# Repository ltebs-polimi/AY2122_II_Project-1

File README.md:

# AY2122_II_Project-1

## Pulseoximeter
The project involves the development of a portable pulseoximeter made using CY8CKIT-059 Development Kit by Cypress/Infineon and the MAX30101, a High-Sensitivity Pulse Oximeter and Heart-Rate Sensor for Wearable Health. Exploiting the circular buffer present inside the sensor, it is possible to extract the values coming from Infrared and Red LEDs and feed them inside a peak detection algorithm for PPG analysis, which outputs the SpO2 and Heart Rate values. Such function has been forked by the [MAX30101_Sensor_Library](https://github.com/sparkfun/SparkFun_MAX3010x_Sensor_Library/blob/master/src/spo2_algorithm.cpp) of the manufacturer Maxim Integrated; the function has been modified to our specific case. 
The project also involved the PCB design and production through press-n-print technique, the 3D case design and printing and the overall assembly of the final case.
## GUI

On the GUI it is also possible to make instant changes to the registers, which directly influence the MAX30101, such as the ADC range, the LED pulse width of the two LEDs, the LEDs pulse amplitude and the Sample Rate. These values will change the Full Scale Range of the readings, as well as the SNR (signal-to-noise-ratio).
## Final assembled device
The final device resembles a commercial pulseoximeter with a rudimental hinge that secures the finger in place over the photodiode, so that a constant pressure is applied. Moreover an internal coating was applied in order not to let light pass, so to assure a reliable sensor measure.

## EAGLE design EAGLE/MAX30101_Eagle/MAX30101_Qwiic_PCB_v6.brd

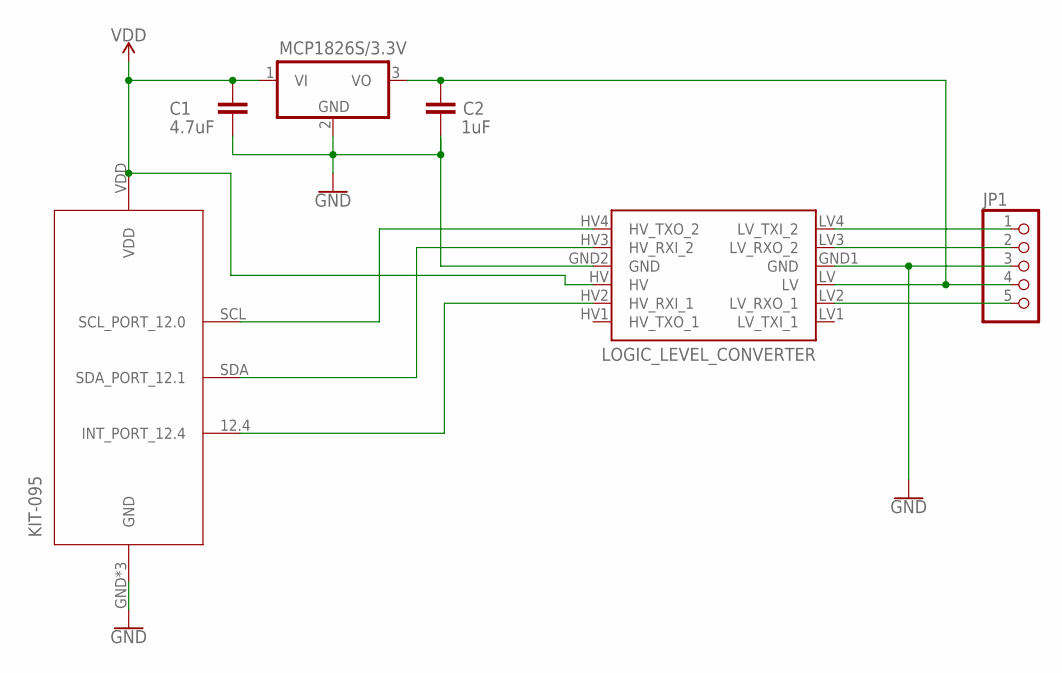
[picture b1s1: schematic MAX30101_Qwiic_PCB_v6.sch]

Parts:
C1: 4.7uF; CAP-PTH-SMALL-KIT
C2: 1uF; CAP-PTH-SMALL-KIT
IC1: 7805T; TO220H
JP1: PINHD-1X5/90; 1X05/90
KIT-095: KIT-095
LOGIC_LEVEL_CONVERTER: SPARKFUN_LOGIC_LEVEL_CONVERTER

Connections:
GND: C1.2, C2.2, IC1.2 (GND), JP1.3, KIT-095.GND, KIT-095.GND_ (GND), KIT-095._GND (GND), LOGIC_LEVEL_CONVERTER.GND1 (GND), LOGIC_LEVEL_CONVERTER.GND2 (GND)
unnamed: C2.1, IC1.3 (VO), JP1.4, LOGIC_LEVEL_CONVERTER.LV
unnamed: KIT-095.SCL (SCL_PORT_12.0), LOGIC_LEVEL_CONVERTER.HV4 (HV_TXO_2)
unnamed: KIT-095.SDA (SDA_PORT_12.1), LOGIC_LEVEL_CONVERTER.HV3 (HV_RXI_2)
unnamed: KIT-095.12.4 (INT_PORT_12.4), LOGIC_LEVEL_CONVERTER.HV2 (HV_RXI_1)
unnamed: JP1.1, LOGIC_LEVEL_CONVERTER.LV4 (LV_TXI_2)
unnamed: JP1.2, LOGIC_LEVEL_CONVERTER.LV3 (LV_RXO_2)
unnamed: JP1.5, LOGIC_LEVEL_CONVERTER.LV2 (LV_RXO_1)
VDD: C1.1, IC1.1 (VI), KIT-095.VDD, LOGIC_LEVEL_CONVERTER.HV

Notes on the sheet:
MCP1826S/3.3V

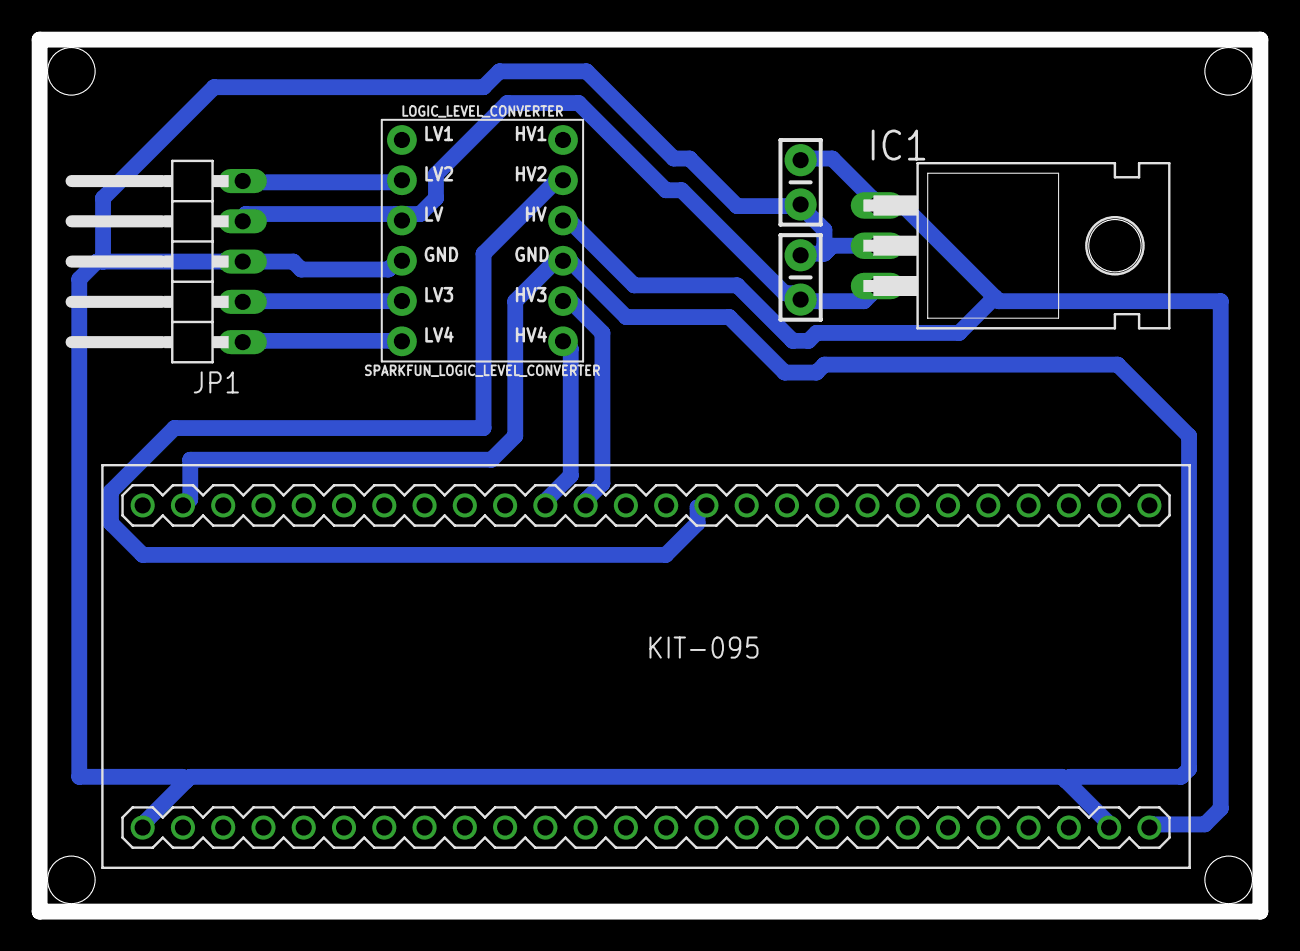
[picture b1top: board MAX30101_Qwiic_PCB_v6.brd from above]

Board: 2 copper layers, 77.0 x 55.0 mm, 6 parts (0 on the bottom side), 9 nets.

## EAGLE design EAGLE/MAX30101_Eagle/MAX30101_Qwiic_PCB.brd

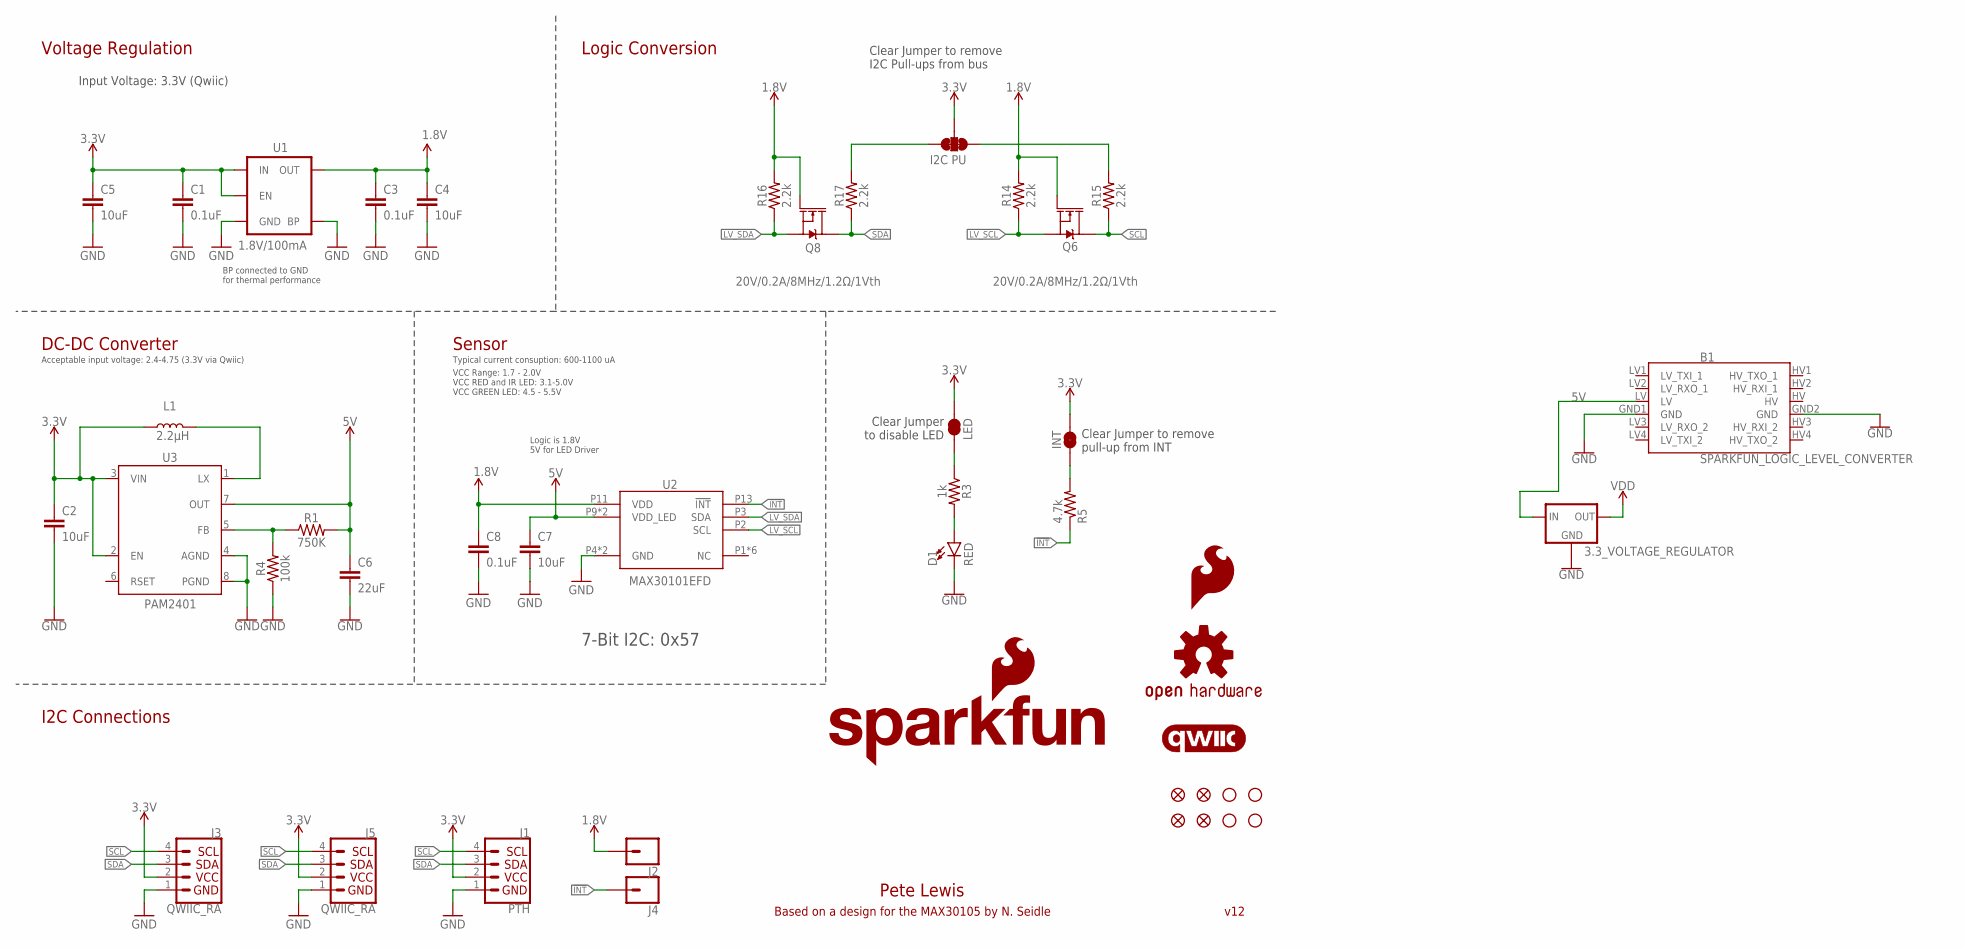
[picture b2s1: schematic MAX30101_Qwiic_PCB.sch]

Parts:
3.3_VOLTAGE_REGULATOR: V_REG_78XX-TO-220; TO-220-ALT
B1: SPARKFUN_LOGIC_LEVEL_CONVERTER
C1, C3, C8: 0.1uF; 0402
C2, C4, C5, C7: 10uF; 0603
C6: 22uF; 0805
D1: RED; LED-0603
FID1, FID2, FID3, FID4: FIDUCIAL1X2; FIDUCIAL-1X2
J1: PTH; 1X04_NO_SILK
J2, J4: CONN_01PTH_NO_SILK_YES_STOP; 1X01_NO_SILK
J3, J5: QWIIC_RA; JST04_1MM_RA
JP1: LED; SMT-JUMPER_2_NC_TRACE_SILK
JP2: INT; SMT-JUMPER_2_NC_TRACE_SILK
JP4: I2C PU; SMT-JUMPER_3_2-NC_TRACE_SILK
L1: 2.2μH; 0806
LOGO1: SFE_LOGO_NAME_FLAME.1_INCH; SFE_LOGO_NAME_FLAME_.1
LOGO2: OSHW-LOGOS; OSHW-LOGO-S
LOGO3: QWIIC_LOGO_5MM; QWIIC_5MM
LOGO4: SFE_LOGO_FLAME.1_INCH; SFE_LOGO_FLAME_.1
Q6, Q8: 20V/0.2A/8MHz/1.2Ω/1Vth; SOT-416FL
R1: 750K; 0603
R3: 1k; 0603
R4: 100k; 0603
R5: 4.7k; 0603
R14, R15, R16, R17: 2.2k; 0603
STANDOFF1, STANDOFF2, STANDOFF3, STANDOFF4: STAND-OFF
U1: 1.8V/100mA; SC70
U2: MAX30101EFD; 14_PIN_OESIP
U3: PAM2401; MSOP8

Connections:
1.8V: C3.1, C4.1, C8.1, J2.1, Q6.1 (G), Q8.1 (G), R14.2, R16.2, U1.5 (OUT), U2.P11 (VDD)
3.3V: C1.1, C2.1, C5.1, J1.2, J3.2, J5.2, JP1.2, JP2.2, JP4.2, L1.1, U1.1 (IN), U1.3 (EN), U3.2 (EN), U3.3 (VIN)
5V: C6.1, C7.1, R1.2, U2.P9 (VDD_LED), U2.P10 (VDD_LED), U3.7 (OUT)
!INT: J4.1, R5.1, U2.P13 (!INT)
GND: 3.3_VOLTAGE_REGULATOR.GND, B1.GND1 (GND), B1.GND2 (GND), C1.2, C2.2, C3.2, C4.2, C5.2, C6.2, C7.2, C8.2, D1.C, J1.1, J3.1, J5.1, R4.1, U1.2 (GND), U1.4 (BP), U2.P4 (GND), U2.P12 (GND), U3.4 (AGND), U3.8 (PGND)
HV: B1.HV
LV_SCL: Q6.2 (S), R14.1, U2.P2 (SCL)
LV_SDA: Q8.2 (S), R16.1, U2.P3 (SDA)
unnamed: JP2.1, R5.2
unnamed: R1.1, R4.2, U3.5 (FB)
unnamed: L1.2, U3.1 (LX)
unnamed: D1.A, R3.2
unnamed: JP4.3, R15.2
unnamed: JP4.1, R17.2
unnamed: 3.3_VOLTAGE_REGULATOR.IN, B1.LV
unnamed: JP1.1, R3.1
SCL: J1.4, J3.4, J5.4, Q6.3 (D), R15.1
SDA: J1.3, J3.3, J5.3, Q8.3 (D), R17.1
VDD: 3.3_VOLTAGE_REGULATOR.OUT

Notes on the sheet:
7-Bit I2C: 0x57
v12
Pete Lewis
Voltage Regulation
Logic Conversion
Sensor
Input Voltage: 3.3V (Qwiic)
Clear Jumper to remove I2C Pull-ups from bus
Clear Jumper to remove pull-up from INT
Logic is 1.8V 5V for LED Driver
BP connected to GND for thermal performance
I2C Connections
Based on a design for the MAX30105 by N. Seidle
Clear Jumper to disable LED
DC-DC Converter
Typical current consuption: 600-1100 uA
VCC Range: 1.7 - 2.0V VCC RED and IR LED: 3.1-5.0V VCC GREEN LED: 4.5 - 5.5V
Acceptable input voltage: 2.4-4.75 (3.3V via Qwiic)

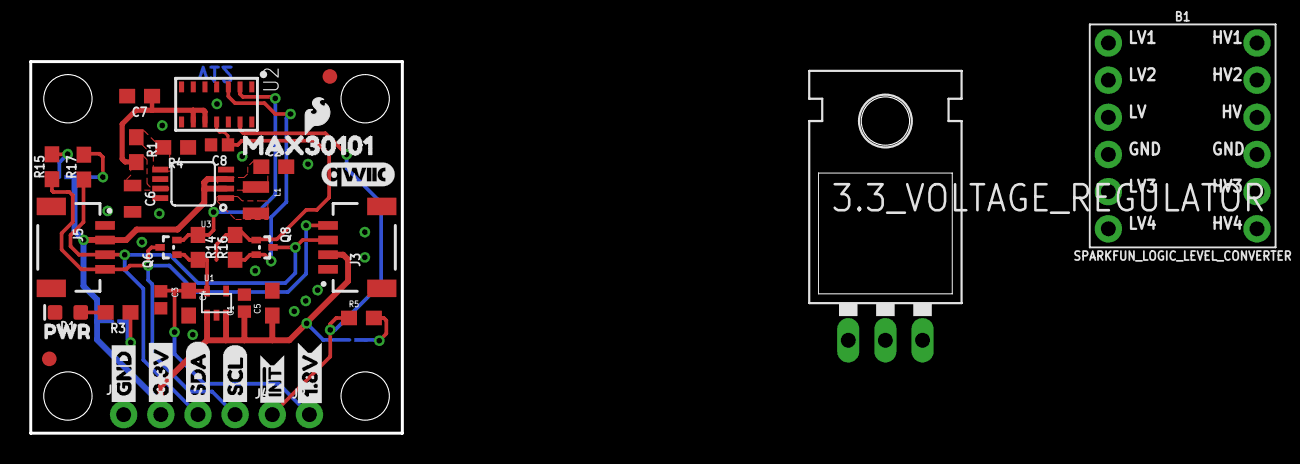
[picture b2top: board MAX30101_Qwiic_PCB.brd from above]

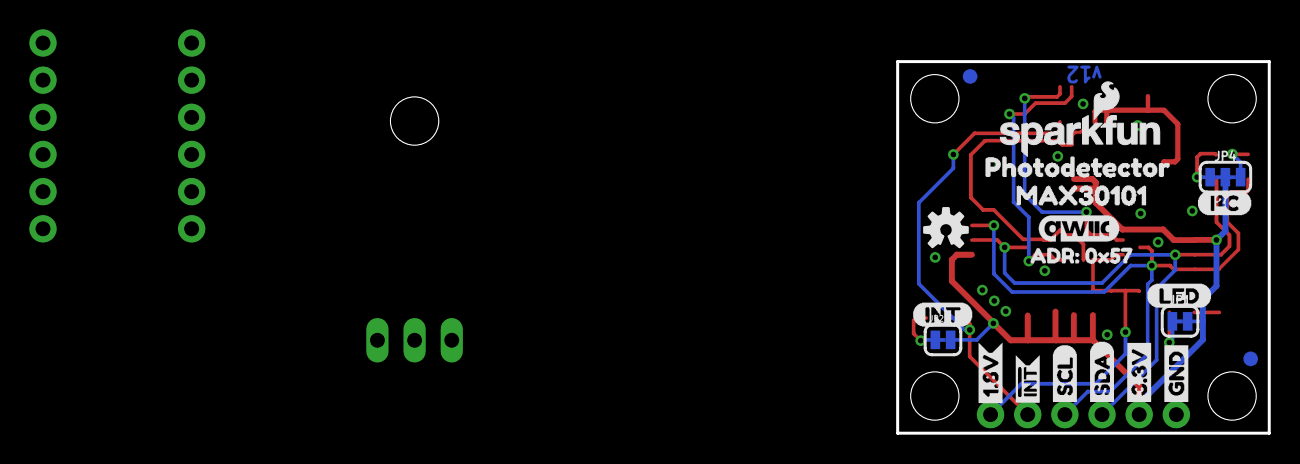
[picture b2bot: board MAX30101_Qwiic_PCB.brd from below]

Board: 2 copper layers, 25.4 x 25.4 mm, 66 parts (20 on the bottom side), 17 nets.

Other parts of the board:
U$1: PHOTODETECTOR3
U$3, U$11: INT#-[<-04
U$4, U$24: MAX301010
U$7: INT-()-04
U$8: LED0
U$9, U$12: SCL-[)
U$10, U$23: GND-04
U$13, U$14: SDA-[)
U$15: ADR#_0X570
U$16: QWIIC_5.5MM
U$19, U$22: 3.3V
U$20, U$27: 1#8V0
U$21: I_SUPER2_C-()-04
U$26: PWR_TO

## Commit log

2022-05-04 First initialization of PSOC workspace
2022-05-04 HeartRate and SPO2 initialization
2022-05-05 initialization of header file with sensor's registries
2022-05-06 Implementation of MAX30101 Libraries.
    Sensor reading is working
2022-05-07 working prototype of MAX30101 library
2022-05-07 bug with file deletion
2022-05-08 print SpO2 inserted
2022-05-09 Added base .gitignore
2022-05-11 implementation of SpO2 and HR calculation in main code but it's not working, needs to be reviewed
2022-05-12 FIFO is filled up to a predefined value and then is all read and printed, must be configured to work with 200 longs array for SpO2 implementation
2022-05-13 spo2 calculation is faulty, needs to be adjusted always outputs -999
2022-05-14 EAGLE - Modifications up to 14/05
2022-05-14 changing the number of FIFOAFull bits doesn't work, 32 bits stops after one full reading of the FIFO, plus changing the resolution of the ADC doesn't work
2022-05-14 without the spo2 part, changing FIFO bits work
2022-05-16 tried to implement the stop at 200 samples inside the readFIFO function (still not working) because it seems that when I choose Pulsewidth of 411 the first reading is of 32 bytes instead of 25 theref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
2022-05-16 Spo2 calculation works at the given setup values and 25 bits of FIFO, haven't tried with different values, but now 411 PW doesn't give problems like it used to, might be because of the specific values
2022-05-16 implementation of a new branch for experimental function that calculates spo2 differently from the previous one. HR still too variable but spo2 value seems to work, must be tried with various configu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
2022-05-17 trying to implement another way to calculate HR to see if this works, millis() function of Arduino is not native in PSOC must be implemented through an interrupt connected to a clock. Must continue w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
2022-05-18 HR function to be developed, trying to plot the data register to see if the values are read accordingly
2022-05-19 PCB - completed
2022-05-19 implementation of HR function with timer and trying to plot signal with BCP
2022-05-19 GUI - list ports
2022-05-19 GUI options - corrected
2022-05-19 the new algorithm for HR doesn't give correct BPM but the count works and also the IR value at the head of the buffer
2022-05-20 Update GUI_options.py
    Inserimento check di controllo sulla tipologia di port; è da ottimizzare la visualizzazione e inserire la connessione automatica a la port trovata tramite il check implementato
2022-05-20 Automatic selection and connection
2022-05-22 GUI - From tutorial
2022-05-24 Solving problems about CheckForBeat function
2022-05-24 Solvin problems about CheckForBeat function
2022-05-24 added new elements to the GUI design, like horizontal sliders to set the parameters of the measurements, plus the click of Start button enable the connection to a COM port, in the example I used COM3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
2022-05-24 GUI - writings in white
2022-05-25 added new file called Photodetector logging test where I implemented the logging instead of the print but I'm not able to make the serial communication work in writing b or s when I press start and s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
2022-05-25 implemented logging function, serial communication doesn't work
2022-05-26 GUI - Photodetector - Restart
2022-05-26 GUI - Slider tutorial
2022-05-27 GUI - graph.py
2022-05-27 added logging test file from wed 25, unable to make the serial connection works in the graph file with PsOc, works with Arduino
2022-05-27 Fixing problems about GetIR function
2022-05-28 file test_GUI funziona la lettura in real time dei dati da un potenziometro, ora bisogna provare a spostare il funzionamento sui dati letti dal FIFO però non dovrebbe cambiare di molto il codice dell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
2022-05-29 GUI with Tkinter + Tutorial Tkinter
2022-05-29 Trying to fix HR problems
2022-05-30 GUI - sliders, SpO2 and HR buttons, Values section, b and s commands
2022-05-30 GUI - Update: Values section + show Parameters when start is clicked
2022-05-31 GUI - Values plotted and visualized
2022-05-31 HR values are different than the true values
2022-05-31 top design
2022-06-01 GUI - different windows for HR and SpO2 values
2022-06-01 plotting raw data
2022-06-02 Better results in terms of HR
2022-06-02 GUI - multiple serial data
2022-06-02 trying to divide the two plots
2022-06-02 print the two values of the buffers from the FIFO to read them with the GUI
2022-06-03 two graph plotting works, by using two flags to divide the values sent. The zoom_test file is to implement the zoom function inside tkinter
2022-06-03 implementation of a toolbar to zoom and save images from the graph
2022-06-03 the next step is to implement the sliders on the GUI which will be connected to the psoc via serial communication of a character
2022-06-03 HR and SPO2 are working
2022-06-03 GUI - unchanged
2022-06-03 3D case - version 2
2022-06-04 3D case - Finished
2022-06-09 USER SETTING
2022-06-09 plotting of two graphs and printing SpO2 and HR values
2022-06-09 plotting IR and RED and print SpO2 and HR work
2022-06-09 we have to implement the setting of parameters from GUI that match the parameters on the PSoC program
2022-06-16 We have to add the GUI part on PSOC
2022-06-17 code must be added to handle the setting of the parameters
2022-06-21 connecting change of registers from GUI to PSoC doesn't work, it is probably related to the interrupts priority
2022-06-24 changing ADC range gets the program stuck but sometimes it works therefore the code makes sense. Tried to implement a global flag activated by the interrupt of received character, so that then the pr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
2022-07-02 GUI - Send char for each setting value
2022-07-02 changing parameters work
2022-07-02 GUI works and images added for the layout
2022-07-05 code works, merge with master
2022-07-05 GUI works, merge next
2022-07-05 Merge branch 'spo2_new_function' of https://github.com/ltebs-polimi/AY2122_II_Project-1 into spo2_new_function
    # Conflicts:
    # Project_LTEBS/Saturimetro.cydsn/BUILD.log
    # Project_LTEBS/Saturimetro.cydsn/SpO2.c
    # Project_LTEBS/Saturimetro.cydsn/TopDesign/TopDesign.cysch
    # Project_LTEBS/Saturimetro.cydsn/USER.c
    # Project_LTEBS/Saturimetro.cydsn/isr.c
2022-07-06 GUI commented
2022-07-06 merging spo2_new_function into master
2022-07-06 deleted unused files
2022-07-06 final GUI
2022-07-06 deleted some files not needed
2022-07-07 Final commented files
2022-07-07 Deleted old/useless files and updated the TopDesign
2022-07-07 Readme - completed
2022-07-14 Presentation link which contains a demo

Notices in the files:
parts and their libraries:
SparkFun-Aesthetics: Licensing: CC v3.0 Share-Alike You are welcome to use this library for commercial purposes.
SparkFun-Resistors: Licensing: Creative Commons ShareAlike 4.0 International - https://creativecommons.org/licenses/by-sa/4.0
